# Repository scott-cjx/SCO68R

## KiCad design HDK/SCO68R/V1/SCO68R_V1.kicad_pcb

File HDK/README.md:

## Planned Features
- USB C
- Rotary Encoders
- SK6812 Neopixel Support
- 32bit controller (ie. STM32)

## Future Planned Features
- BLE
- Multi-USB Support
- OLED Display

## Inception
- Inspiration layout: TM680

- Selected MCU: STM32F103C8T6
    - MCU has 4 timers with STM's "Encoder Mode", SCO68R can support up to 4 rotary encoders.

## Obstacles
- Neopixel (WS2812 & SK6812) runs on 5v logic whereas STM32 runs on 3.3v logic. 
    - Transistor level shifter circuit is added [(Level Shifter Circuit)](https://learn.sparkfun.com/tutorials/bi-directional-logic-level-converter-hookup-guide/all)
    - 

## BOM

@@include[bom.md](includes/my-file.md)

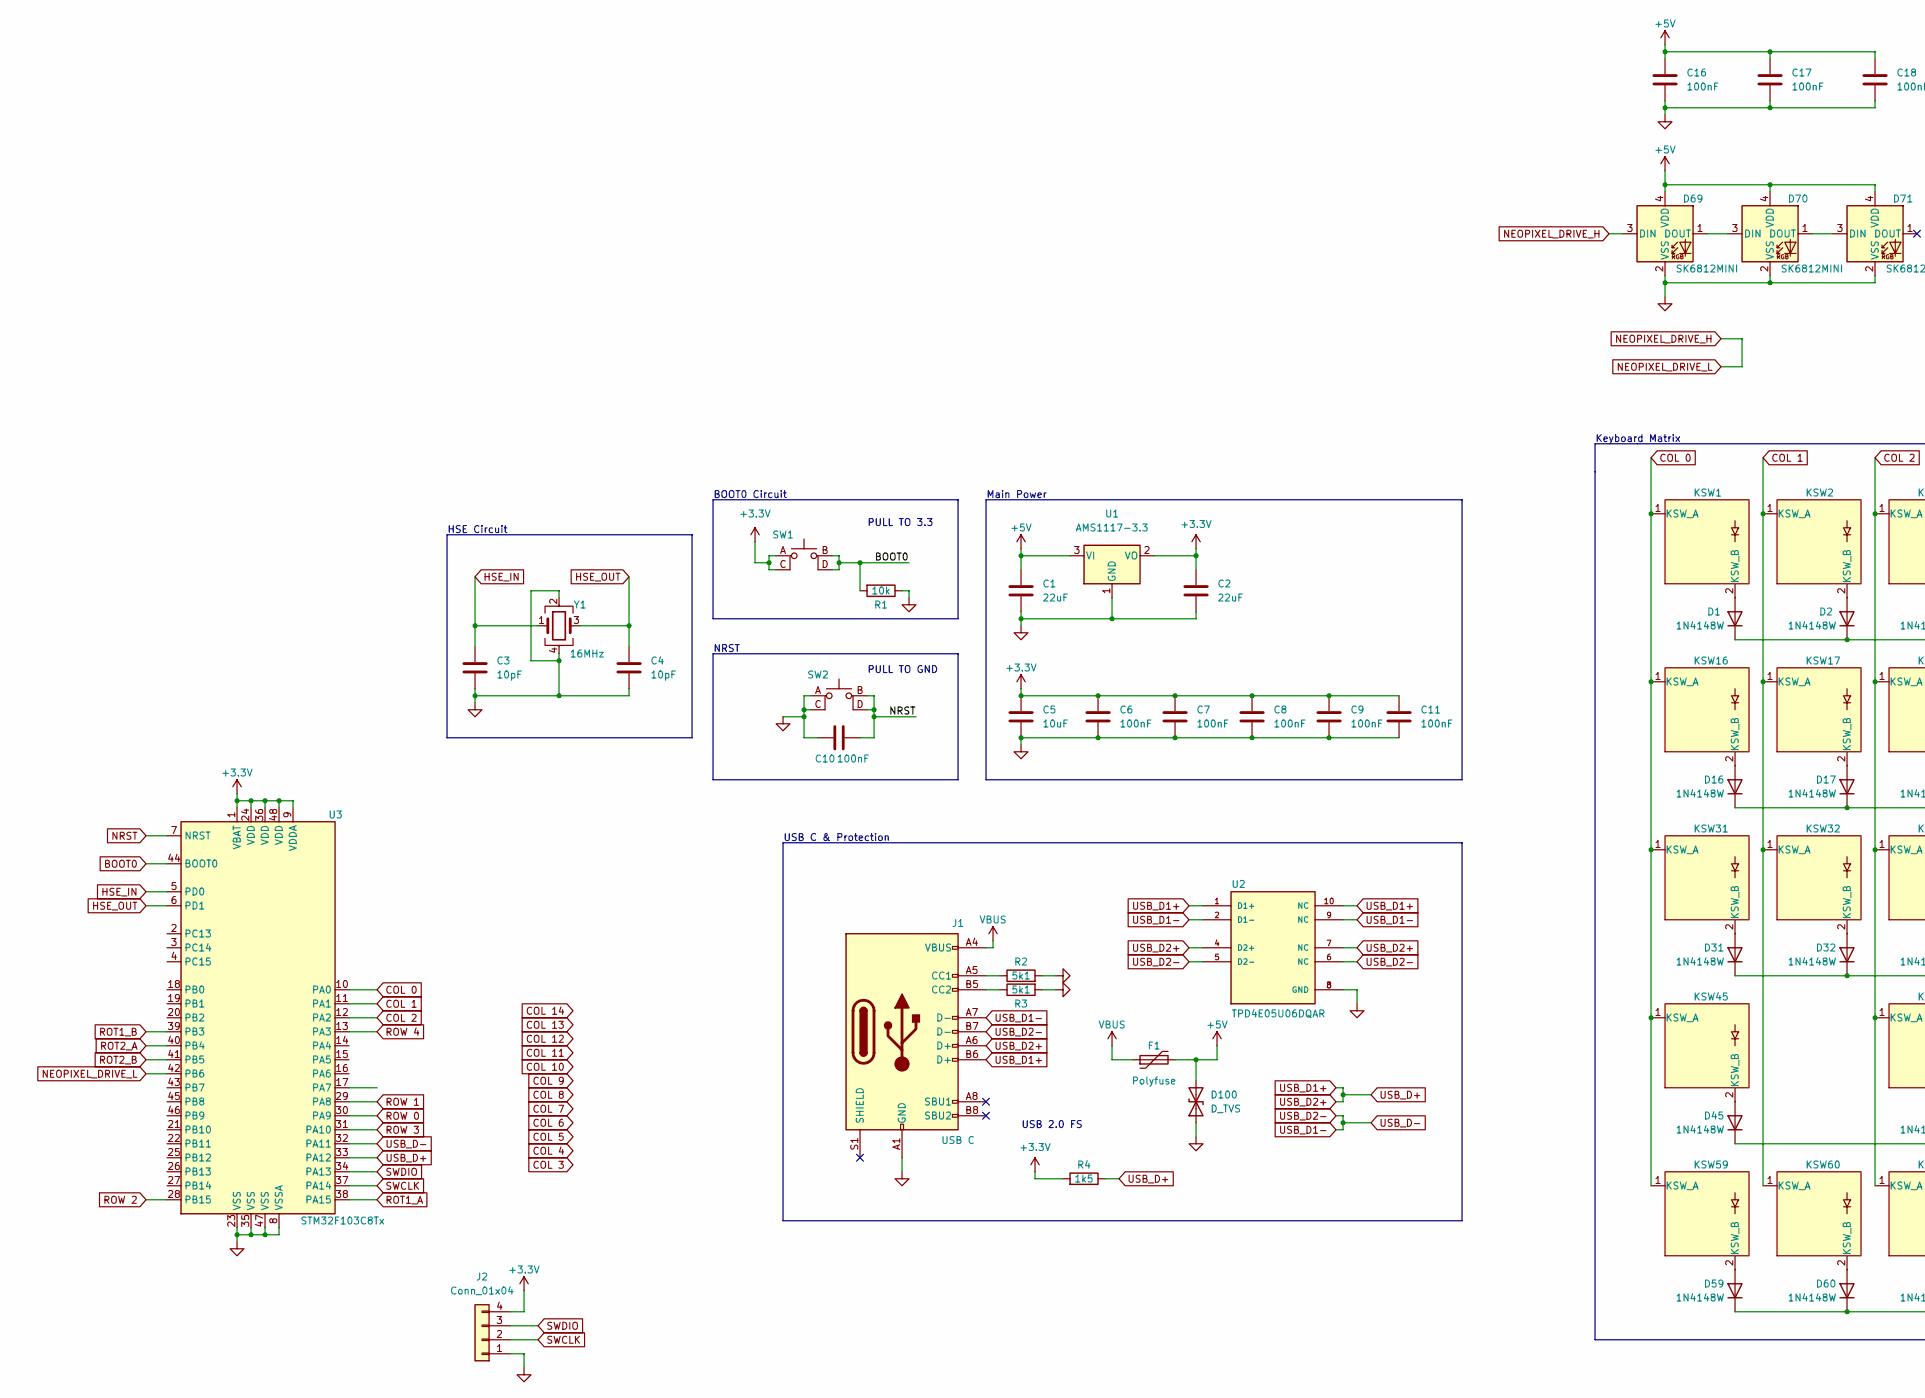
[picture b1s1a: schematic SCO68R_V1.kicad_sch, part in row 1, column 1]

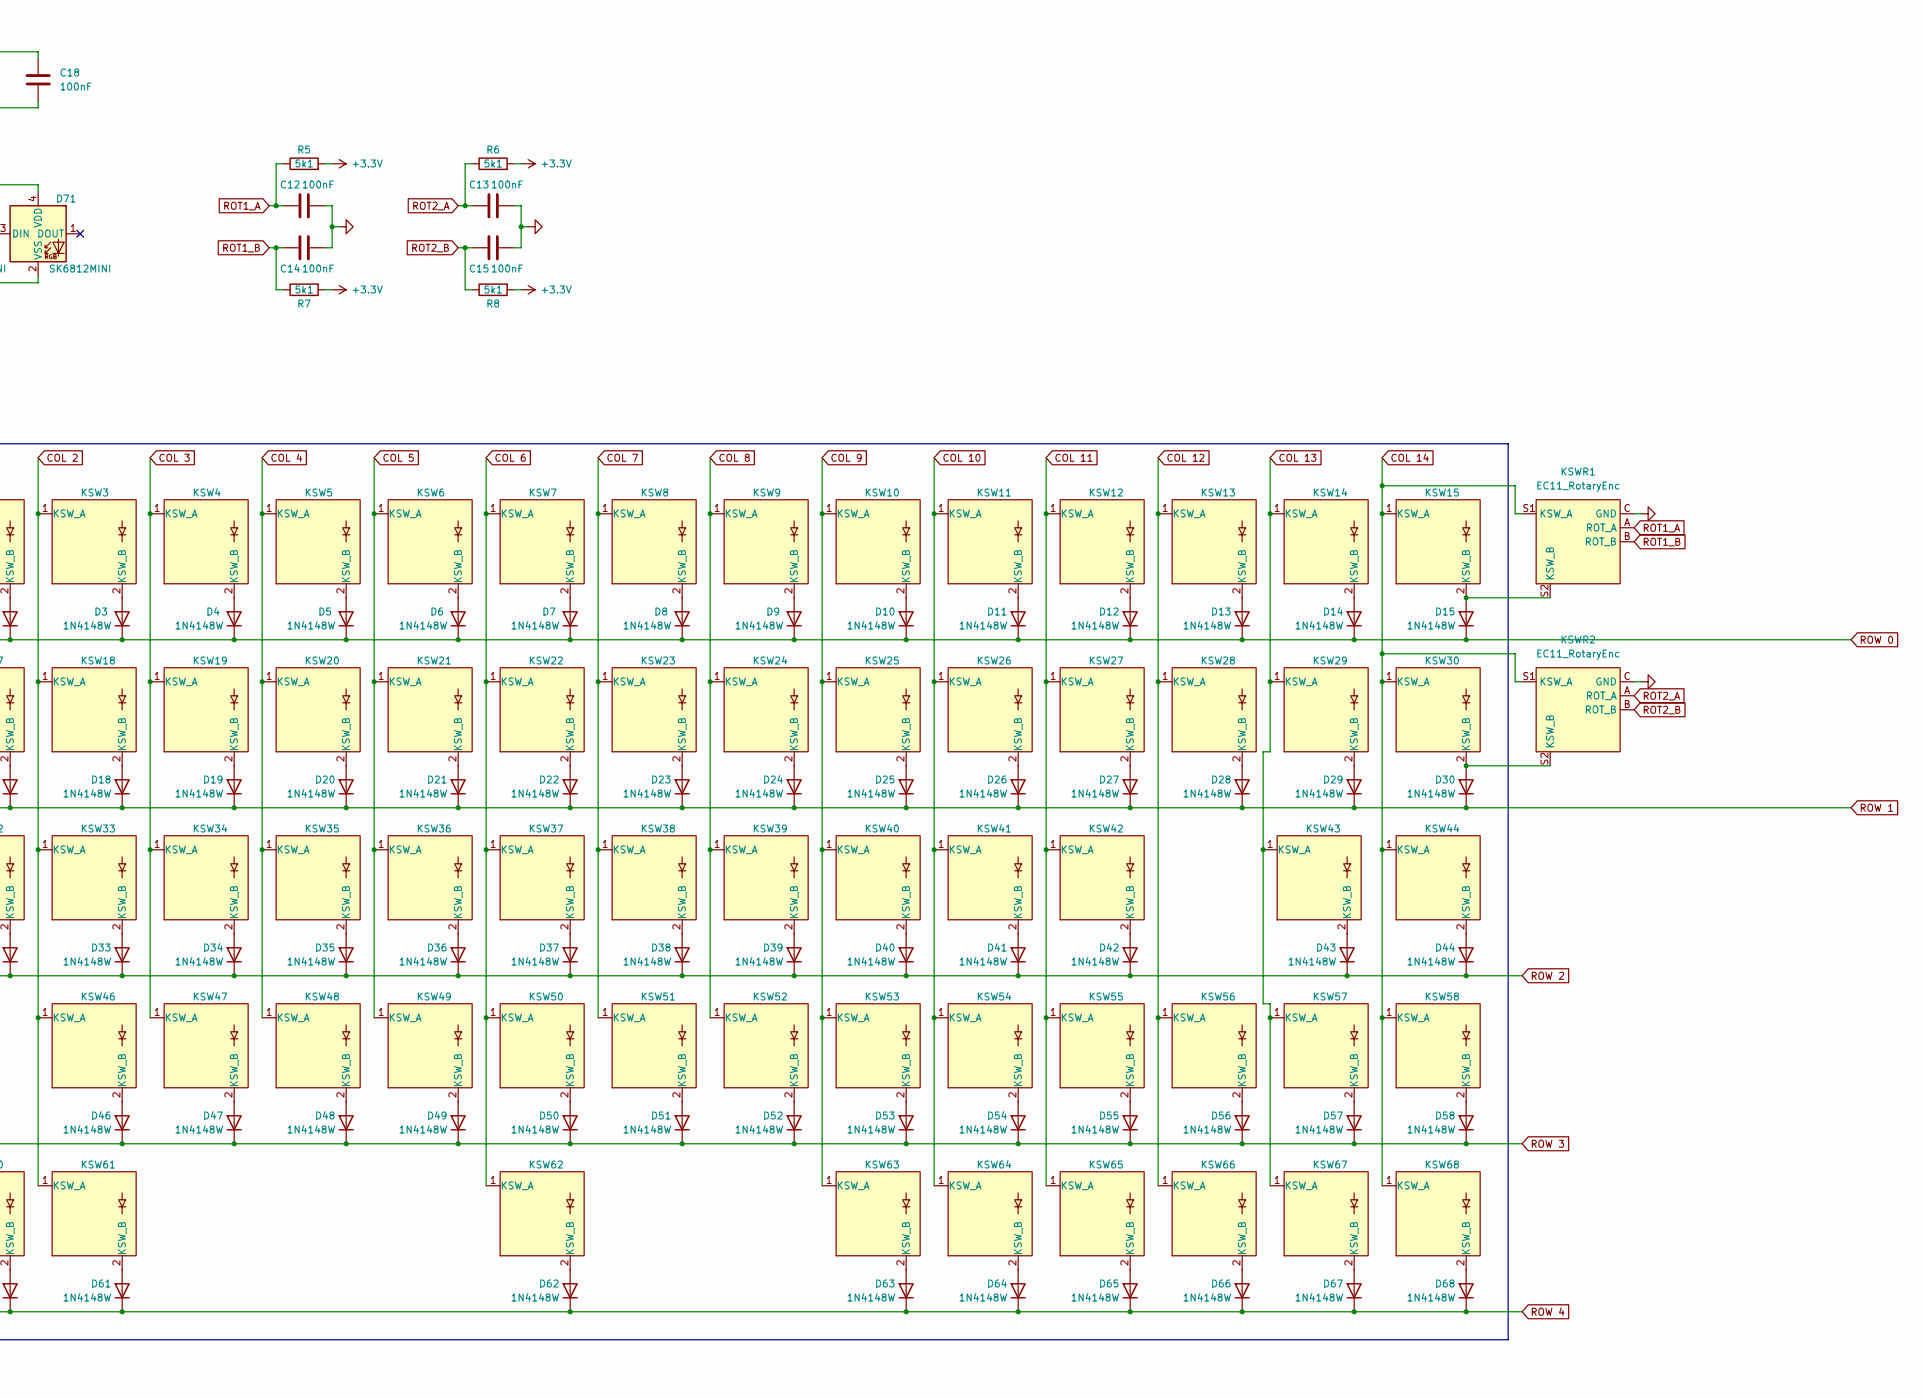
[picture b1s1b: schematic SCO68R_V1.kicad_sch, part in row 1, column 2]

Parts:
C1, C2: 22uF; C_1206_3216Metric_Pad1.33x1.80mm_HandSolder
C3, C4: 10pF; C_0805_2012Metric_Pad1.18x1.45mm_HandSolder
C5: 10uF; C_0603_1608Metric_Pad1.08x0.95mm_HandSolder
C6, C7, C8, C9, C10, C11, C12, C13, C14, C15, C16, C17, C18: 100nF; C_0402_1005Metric_Pad0.74x0.62mm_HandSolder
D1, D2, D3, D4, D5, D6, D7, D8, D9, D10, D11, D12, D13, D14, D15, D16, D17, D18, D19, D20, D21, D22, D23, D24, D25, D26, D27, D28, D29, D30, D31, D32, D33, D34, D35, D36, D37, D38, D39, D40, D41, D42, D43, D44, D45, D46, D47, D48, D49, D50, D51, D52, D53, D54, D55, D56, D57, D58, D59, D60, D61, D62, D63, D64, D65, D66, D67, D68: 1N4148W; D_SOD-123
D69, D70, D71: SK6812MINI; LED_SK6812MINI_PLCC4_3.5x3.5mm_P1.75mm
D100: D_TVS; D_SOD-123F
F1: Polyfuse; Fuse_1206_3216Metric_Pad1.42x1.75mm_HandSolder
J1: USB C; USB_C_Receptacle_HRO_TYPE-C-31-M-12
J2: Conn_01x04; PinHeader_1x04_P2.54mm_Vertical
KSW1, KSW2, KSW3, KSW4, KSW5, KSW6, KSW7, KSW8, KSW9, KSW10, KSW11, KSW12, KSW13, KSW14, KSW15, KSW16, KSW17, KSW18, KSW19, KSW20, KSW21, KSW22, KSW23, KSW24, KSW25, KSW26, KSW27, KSW28, KSW29, KSW30, KSW31, KSW32, KSW33, KSW34, KSW35, KSW36, KSW37, KSW38, KSW39, KSW40, KSW41, KSW42, KSW43, KSW44, KSW45, KSW46, KSW47, KSW48, KSW49, KSW50, KSW51, KSW52, KSW53, KSW54, KSW55, KSW56, KSW57, KSW58, KSW59, KSW60, KSW61, KSW62, KSW63, KSW64, KSW65, KSW66, KSW67, KSW68: Keyswitch_&_Diode; 1.00U_MX-MILLMAX_3305
KSWR1, KSWR2: EC11_RotaryEnc; RotaryEncoder_Alps_EC11E-Switch_Vertical_H20mm
R1: 10k; R_0402_1005Metric_Pad0.72x0.64mm_HandSolder
R2, R3, R5, R6, R7, R8: 5k1; R_0402_1005Metric_Pad0.72x0.64mm_HandSolder
R4: 1k5; R_0402_1005Metric_Pad0.72x0.64mm_HandSolder
SW1, SW2: SW_MEC_5E; SW_TS-1187A-B-A-B
U1: AMS1117-3.3; SOT-223-3_TabPin2
U2: TPD4E05U06DQAR; TI_TPD4E05U06DQAR
U3: STM32F103C8Tx; LQFP-48_7x7mm_P0.5mm
Y1: 16MHz; Crystal_SMD_3225-4Pin_3.2x2.5mm_HandSoldering

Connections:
+3.3V: C2.1, C5.1, C6.1, C7.1, C8.1, C9.1, C11.1, J2.4, R4.2, R5.2, R6.2, R7.2, R8.2, SW1.A (1), SW1.C (2), U1.2 (VO), U3.1 (VBAT), U3.9 (VDDA), U3.24 (VDD), U3.36 (VDD), U3.48 (VDD)
+5V: C1.1, C16.1, C17.1, C18.1, D69.4 (VDD), D70.4 (VDD), D71.4 (VDD), D100.2 (A2), F1.2, U1.3 (VI)
BOOT0: R1.2, SW1.B (4), SW1.D (3), U3.44 (BOOT0)
COL 0: KSW1.1 (KSW_A), KSW16.1 (KSW_A), KSW31.1 (KSW_A), KSW45.1 (KSW_A), KSW59.1 (KSW_A), U3.10 (PA0)
COL 1: KSW2.1 (KSW_A), KSW17.1 (KSW_A), KSW32.1 (KSW_A), KSW60.1 (KSW_A), U3.11 (PA1)
COL 2: KSW3.1 (KSW_A), KSW18.1 (KSW_A), KSW33.1 (KSW_A), KSW46.1 (KSW_A), KSW61.1 (KSW_A), U3.12 (PA2)
COL 3: KSW4.1 (KSW_A), KSW19.1 (KSW_A), KSW34.1 (KSW_A), KSW47.1 (KSW_A)
COL 4: KSW5.1 (KSW_A), KSW20.1 (KSW_A), KSW35.1 (KSW_A), KSW48.1 (KSW_A)
COL 5: KSW6.1 (KSW_A), KSW21.1 (KSW_A), KSW36.1 (KSW_A), KSW49.1 (KSW_A)
COL 6: KSW7.1 (KSW_A), KSW22.1 (KSW_A), KSW37.1 (KSW_A), KSW50.1 (KSW_A), KSW62.1 (KSW_A)
COL 7: KSW8.1 (KSW_A), KSW23.1 (KSW_A), KSW38.1 (KSW_A), KSW51.1 (KSW_A)
COL 8: KSW9.1 (KSW_A), KSW24.1 (KSW_A), KSW39.1 (KSW_A), KSW52.1 (KSW_A)
COL 9: KSW10.1 (KSW_A), KSW25.1 (KSW_A), KSW40.1 (KSW_A), KSW53.1 (KSW_A), KSW63.1 (KSW_A)
COL 10: KSW11.1 (KSW_A), KSW26.1 (KSW_A), KSW41.1 (KSW_A), KSW54.1 (KSW_A), KSW64.1 (KSW_A)
COL 11: KSW12.1 (KSW_A), KSW27.1 (KSW_A), KSW42.1 (KSW_A), KSW55.1 (KSW_A), KSW65.1 (KSW_A)
COL 12: KSW13.1 (KSW_A), KSW28.1 (KSW_A), KSW56.1 (KSW_A), KSW66.1 (KSW_A)
COL 13: KSW14.1 (KSW_A), KSW29.1 (KSW_A), KSW43.1 (KSW_A), KSW57.1 (KSW_A), KSW67.1 (KSW_A)
COL 14: KSW15.1 (KSW_A), KSW30.1 (KSW_A), KSW44.1 (KSW_A), KSW58.1 (KSW_A), KSW68.1 (KSW_A), KSWR1.S1 (KSW_A), KSWR2.S1 (KSW_A)
GND: C1.2, C2.2, C3.2, C4.2, C5.2, C6.2, C7.2, C8.2, C9.2, C10.1, C11.2, C12.1, C13.1, C14.2, C15.2, C16.2, C17.2, C18.2, D69.2 (VSS), D70.2 (VSS), D71.2 (VSS), D100.1 (A1), J1.A1 (GND), J1.A12 (GND), J1.B1 (GND), J1.B12 (GND), J2.1, KSWR1.C (GND), KSWR2.C (GND), R1.1, R2.2, R3.2, SW2.A (1), SW2.C (2), U1.1 (GND), U2.3 (GND), U2.8 (GND), U3.8 (VSSA), U3.23 (VSS), U3.35 (VSS), U3.47 (VSS), Y1.2, Y1.4
HSE_IN: C3.1, U3.5 (PD0), Y1.1
HSE_OUT: C4.1, U3.6 (PD1), Y1.3
NEOPIXEL_DRIVE_H: D69.3 (DIN), U3.42 (PB6)
NRST: C10.2, SW2.B (4), SW2.D (3), U3.7 (NRST)
unnamed: D1.2 (A), KSW1.2 (KSW_B)
unnamed: D2.2 (A), KSW2.2 (KSW_B)
unnamed: D3.2 (A), KSW3.2 (KSW_B)
unnamed: D4.2 (A), KSW4.2 (KSW_B)
unnamed: D5.2 (A), KSW5.2 (KSW_B)
unnamed: D6.2 (A), KSW6.2 (KSW_B)
unnamed: D7.2 (A), KSW7.2 (KSW_B)
unnamed: D8.2 (A), KSW8.2 (KSW_B)
unnamed: D9.2 (A), KSW9.2 (KSW_B)
unnamed: D10.2 (A), KSW10.2 (KSW_B)
unnamed: D11.2 (A), KSW11.2 (KSW_B)
unnamed: D12.2 (A), KSW12.2 (KSW_B)
unnamed: D13.2 (A), KSW13.2 (KSW_B)
unnamed: D14.2 (A), KSW14.2 (KSW_B)
unnamed: D15.2 (A), KSW15.2 (KSW_B), KSWR1.S2 (KSW_B)
unnamed: D16.2 (A), KSW16.2 (KSW_B)
unnamed: D17.2 (A), KSW17.2 (KSW_B)
unnamed: D18.2 (A), KSW18.2 (KSW_B)
unnamed: D19.2 (A), KSW19.2 (KSW_B)
unnamed: D20.2 (A), KSW20.2 (KSW_B)
unnamed: D21.2 (A), KSW21.2 (KSW_B)
unnamed: D22.2 (A), KSW22.2 (KSW_B)
unnamed: D23.2 (A), KSW23.2 (KSW_B)
unnamed: D24.2 (A), KSW24.2 (KSW_B)
unnamed: D25.2 (A), KSW25.2 (KSW_B)
unnamed: D26.2 (A), KSW26.2 (KSW_B)
unnamed: D27.2 (A), KSW27.2 (KSW_B)
unnamed: D28.2 (A), KSW28.2 (KSW_B)
unnamed: D29.2 (A), KSW29.2 (KSW_B)
unnamed: D30.2 (A), KSW30.2 (KSW_B), KSWR2.S2 (KSW_B)
unnamed: D31.2 (A), KSW31.2 (KSW_B)
unnamed: D32.2 (A), KSW32.2 (KSW_B)
unnamed: D33.2 (A), KSW33.2 (KSW_B)
unnamed: D34.2 (A), KSW34.2 (KSW_B)
unnamed: D35.2 (A), KSW35.2 (KSW_B)
unnamed: D36.2 (A), KSW36.2 (KSW_B)
unnamed: D37.2 (A), KSW37.2 (KSW_B)
unnamed: D38.2 (A), KSW38.2 (KSW_B)
unnamed: D39.2 (A), KSW39.2 (KSW_B)
unnamed: D40.2 (A), KSW40.2 (KSW_B)
unnamed: D41.2 (A), KSW41.2 (KSW_B)
unnamed: D42.2 (A), KSW42.2 (KSW_B)
unnamed: D43.2 (A), KSW43.2 (KSW_B)
unnamed: D44.2 (A), KSW44.2 (KSW_B)
unnamed: D45.2 (A), KSW45.2 (KSW_B)
unnamed: D46.2 (A), KSW46.2 (KSW_B)
unnamed: D47.2 (A), KSW47.2 (KSW_B)
unnamed: D48.2 (A), KSW48.2 (KSW_B)
unnamed: D49.2 (A), KSW49.2 (KSW_B)
unnamed: D50.2 (A), KSW50.2 (KSW_B)
unnamed: D51.2 (A), KSW51.2 (KSW_B)
unnamed: D52.2 (A), KSW52.2 (KSW_B)
unnamed: D53.2 (A), KSW53.2 (KSW_B)
unnamed: D54.2 (A), KSW54.2 (KSW_B)
unnamed: D55.2 (A), KSW55.2 (KSW_B)
unnamed: D56.2 (A), KSW56.2 (KSW_B)
unnamed: D57.2 (A), KSW57.2 (KSW_B)
unnamed: D58.2 (A), KSW58.2 (KSW_B)
unnamed: D59.2 (A), KSW59.2 (KSW_B)
unnamed: D60.2 (A), KSW60.2 (KSW_B)
unnamed: D61.2 (A), KSW61.2 (KSW_B)
unnamed: D62.2 (A), KSW62.2 (KSW_B)
unnamed: D63.2 (A), KSW63.2 (KSW_B)
unnamed: D64.2 (A), KSW64.2 (KSW_B)
unnamed: D65.2 (A), KSW65.2 (KSW_B)
unnamed: D66.2 (A), KSW66.2 (KSW_B)
unnamed: D67.2 (A), KSW67.2 (KSW_B)
unnamed: D68.2 (A), KSW68.2 (KSW_B)
unnamed: D69.1 (DOUT), D70.3 (DIN)
unnamed: D70.1 (DOUT), D71.3 (DIN)
unnamed: J1.A5 (CC1), R2.1
unnamed: J1.B5 (CC2), R3.1
ROT1_A: C12.2, KSWR1.A (ROT_A), R5.1, U3.38 (PA15)
ROT1_B: C14.1, KSWR1.B (ROT_B), R7.1, U3.39 (PB3)
ROT2_A: C13.2, KSWR2.A (ROT_A), R6.1, U3.40 (PB4)
ROT2_B: C15.1, KSWR2.B (ROT_B), R8.1, U3.41 (PB5)
ROW 0: D1.1 (K), D2.1 (K), D3.1 (K), D4.1 (K), D5.1 (K), D6.1 (K), D7.1 (K), D8.1 (K), D9.1 (K), D10.1 (K), D11.1 (K), D12.1 (K), D13.1 (K), D14.1 (K), D15.1 (K), U3.30 (PA9)
ROW 1: D16.1 (K), D17.1 (K), D18.1 (K), D19.1 (K), D20.1 (K), D21.1 (K), D22.1 (K), D23.1 (K), D24.1 (K), D25.1 (K), D26.1 (K), D27.1 (K), D28.1 (K), D29.1 (K), D30.1 (K), U3.29 (PA8)
ROW 2: D31.1 (K), D32.1 (K), D33.1 (K), D34.1 (K), D35.1 (K), D36.1 (K), D37.1 (K), D38.1 (K), D39.1 (K), D40.1 (K), D41.1 (K), D42.1 (K), D43.1 (K), D44.1 (K), U3.28 (PB15)
ROW 3: D45.1 (K), D46.1 (K), D47.1 (K), D48.1 (K), D49.1 (K), D50.1 (K), D51.1 (K), D52.1 (K), D53.1 (K), D54.1 (K), D55.1 (K), D56.1 (K), D57.1 (K), D58.1 (K), U3.31 (PA10)
ROW 4: D59.1 (K), D60.1 (K), D61.1 (K), D62.1 (K), D63.1 (K), D64.1 (K), D65.1 (K), D66.1 (K), D67.1 (K), D68.1 (K), U3.13 (PA3)
SWCLK: J2.2, U3.37 (PA14)
SWDIO: J2.3, U3.34 (PA13)
USB_D+: J1.A6 (D+), J1.B6 (D+), R4.1, U2.1 (D1+), U2.4 (D2+), U2.7 (NC), U2.10 (NC), U3.33 (PA12)
USB_D-: J1.A7 (D-), J1.B7 (D-), U2.2 (D1-), U2.5 (D2-), U2.6 (NC), U2.9 (NC), U3.32 (PA11)
VBUS: F1.1, J1.A4 (VBUS), J1.A9 (VBUS), J1.B4 (VBUS), J1.B9 (VBUS)

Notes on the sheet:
PULL TO 3.3
USB C & Protection
Main Power
HSE Circuit
NRST
BOOT0 Circuit
USB 2.0 FS
Keyboard Matrix
PULL TO GND

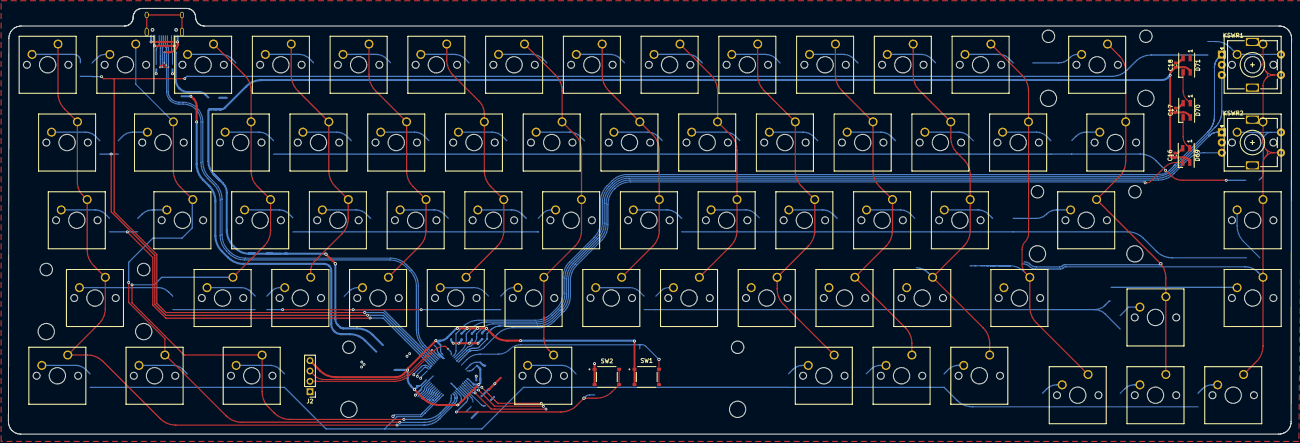
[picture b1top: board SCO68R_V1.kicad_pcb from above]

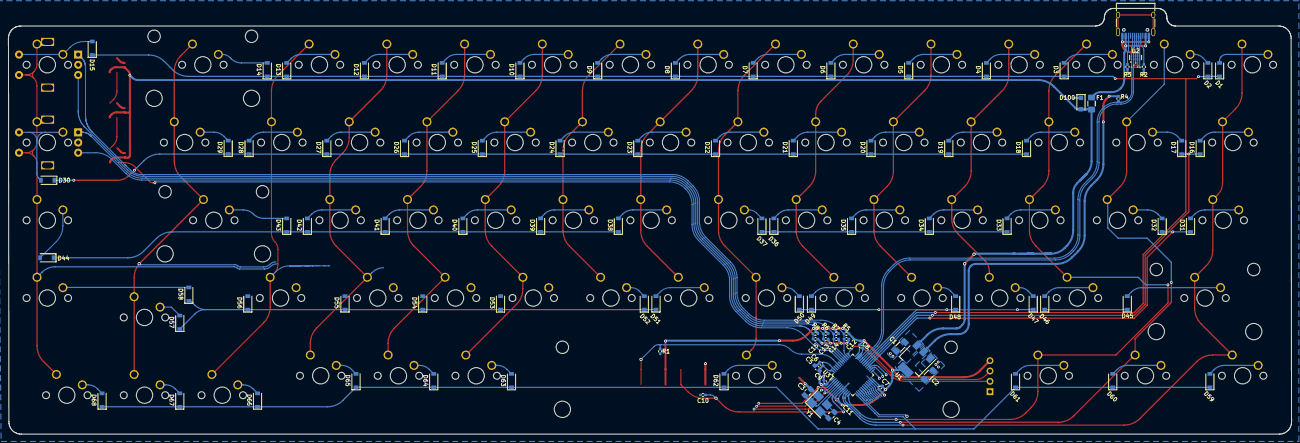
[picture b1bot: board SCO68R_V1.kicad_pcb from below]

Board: 2 copper layers, 314.4 x 104.3 mm, 177 parts (98 on the bottom side), 109 nets.

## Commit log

2022-07-19 Added SCO68R HDK
2022-07-19 edited HDK/README.md
2022-07-20 Edited HDK
2022-07-20 Added Fully Routed V1F
2022-07-20 Added Finishing Touches
2022-07-23 Edited Docs
